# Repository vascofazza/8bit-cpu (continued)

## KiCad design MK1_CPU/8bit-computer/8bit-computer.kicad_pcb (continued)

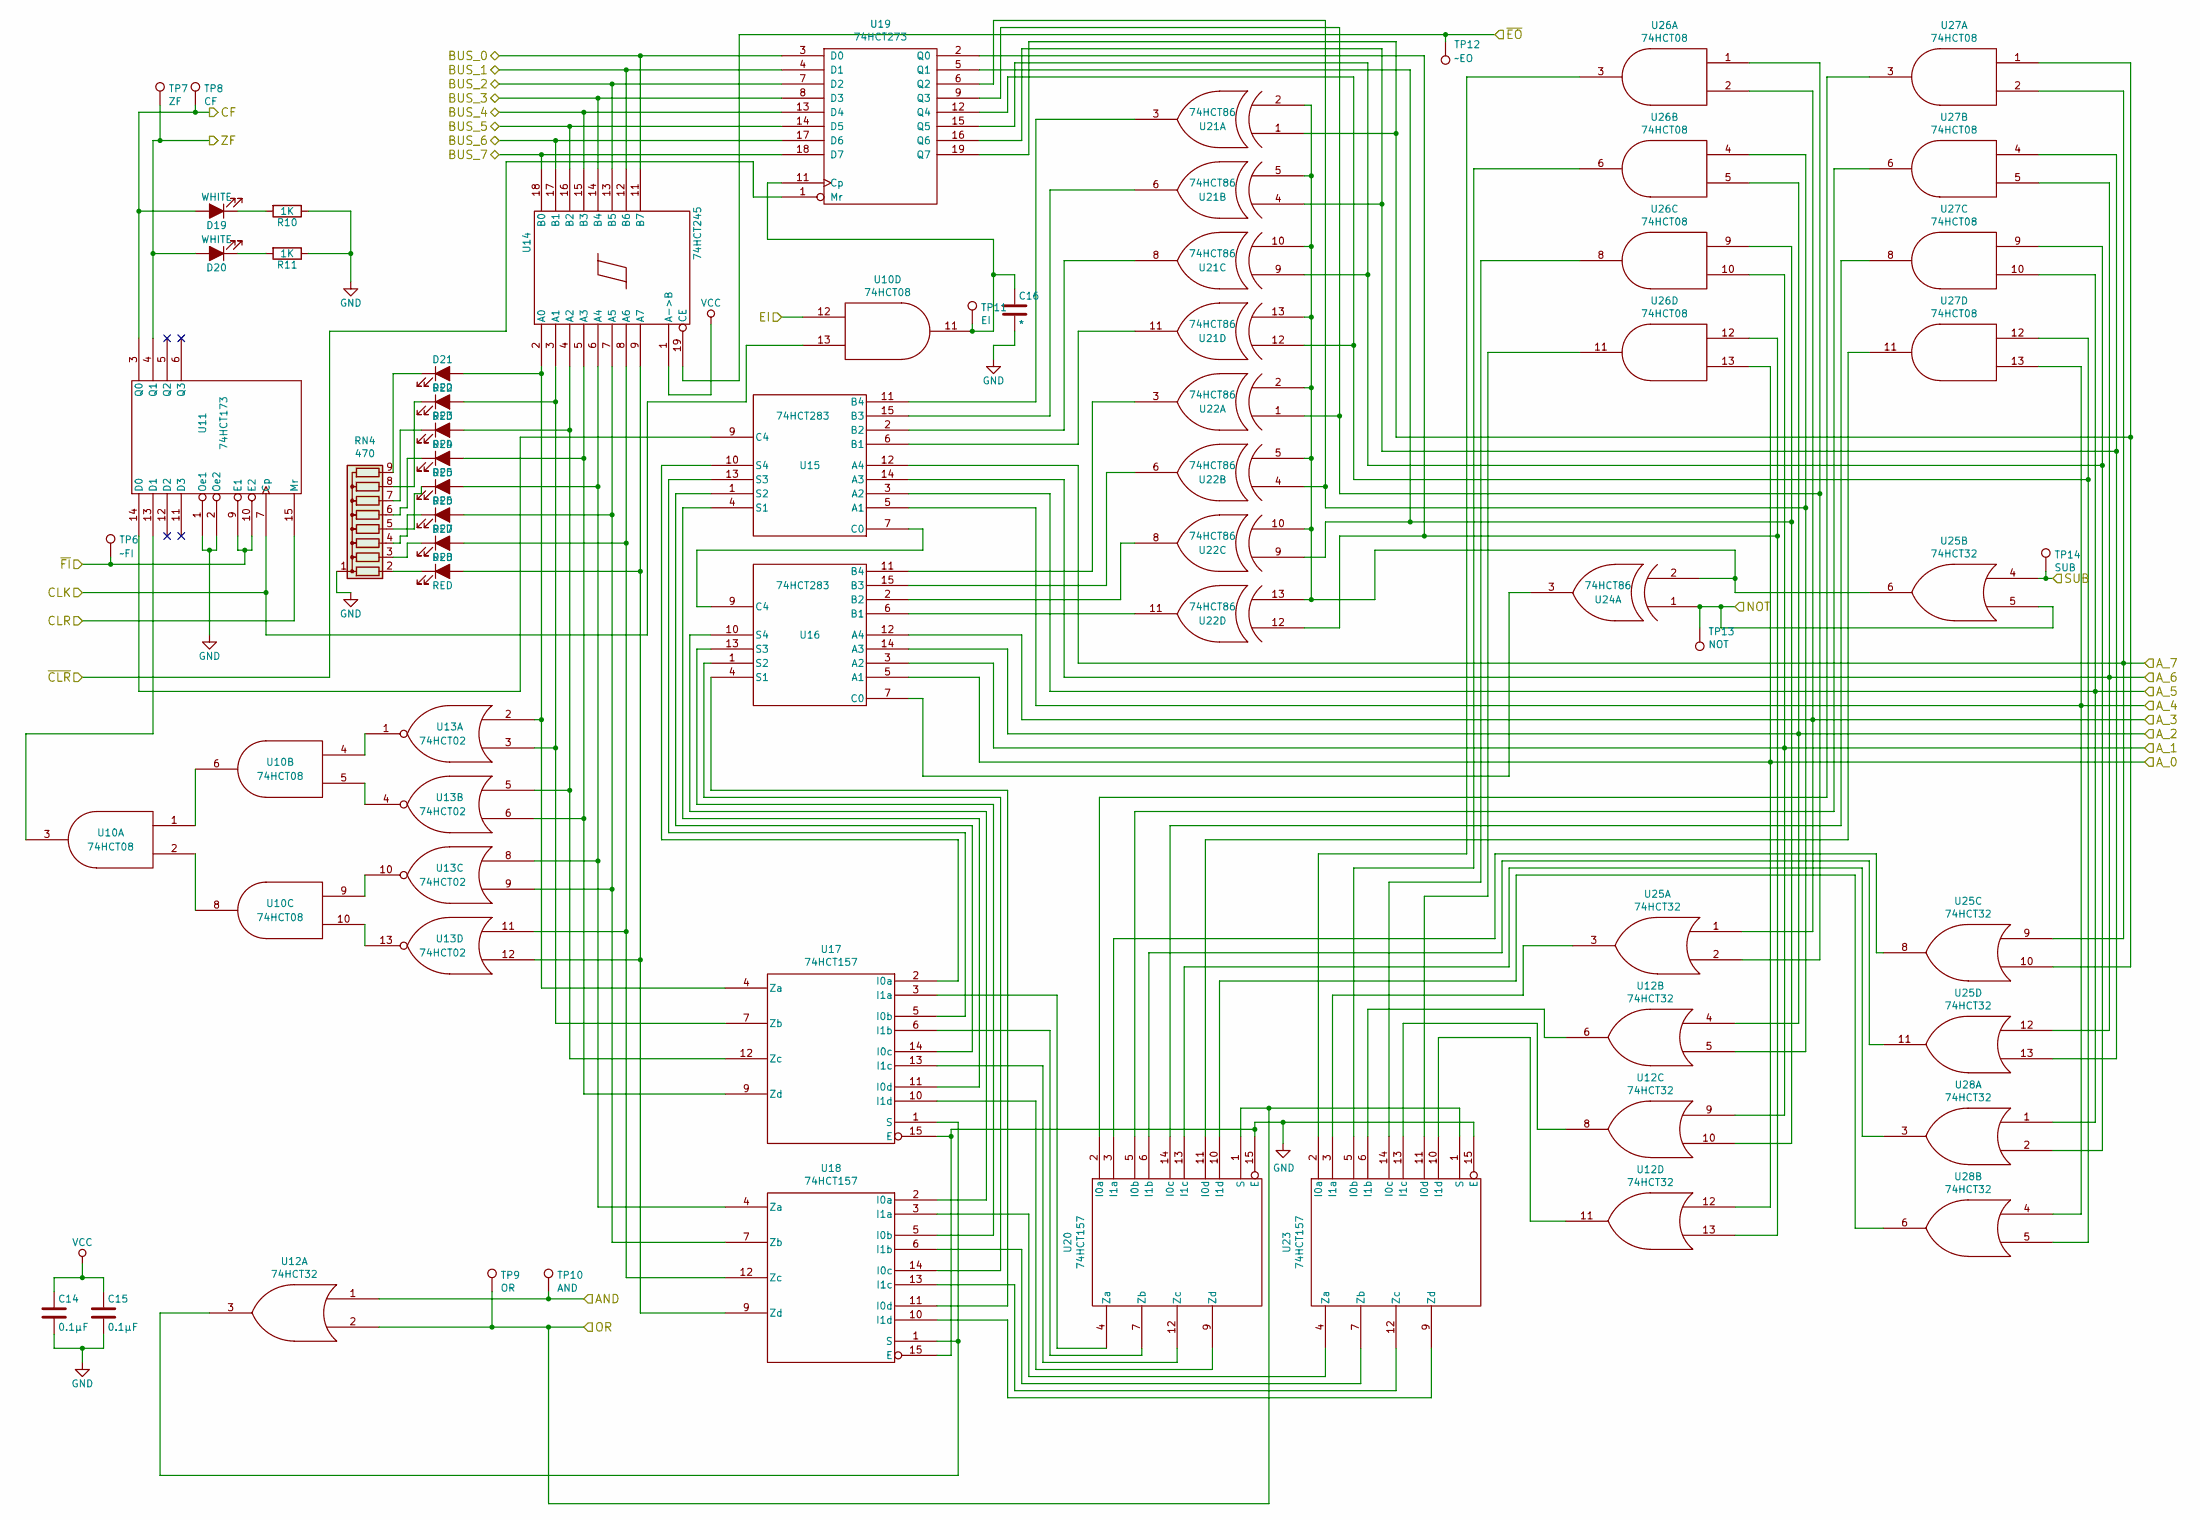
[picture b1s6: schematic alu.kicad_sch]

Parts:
C14, C15: 0.1µF; C_Disc_D4.3mm_W1.9mm_P5.00mm
C16: *; C_Disc_D4.3mm_W1.9mm_P5.00mm
D19, D20: WHITE; LED_D3.0mm
D21, D22, D23, D24, D25, D26, D27, D28: RED; LED_D3.0mm
R10, R11: 1K; R_Axial_DIN0207_L6.3mm_D2.5mm_P7.62mm_Horizontal
RN4: 470; R_Array_SIP9
TP6: ~FI; TestPoint_Pad_1.0x1.0mm
TP7: ZF; TestPoint_Pad_1.0x1.0mm
TP8: CF; TestPoint_Pad_1.0x1.0mm
TP9: OR; TestPoint_Pad_1.0x1.0mm
TP10: AND; TestPoint_Pad_1.0x1.0mm
TP11: EI; TestPoint_Pad_1.0x1.0mm
TP12: ~EO; TestPoint_Pad_1.0x1.0mm
TP13: NOT; TestPoint_Pad_1.0x1.0mm
TP14: SUB; TestPoint_Pad_1.0x1.0mm
U10, U26, U27: 74HCT08; DIP-14_W7.62mm
U11: 74HCT173; DIP-16_W7.62mm
U12, U25, U28: 74HCT32; DIP-14_W7.62mm
U13: 74HCT02; DIP-14_W7.62mm
U14: 74HCT245; DIP-20_W7.62mm
U15, U16: 74HCT283; DIP-16_W7.62mm
U17, U18, U20, U23: 74HCT157; DIP-16_W7.62mm
U19: 74HCT273; DIP-20_W7.62mm
U21, U22, U24: 74HCT86; DIP-14_W7.62mm

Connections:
/ALU/CF: D19.2 (A), TP8.1, U11.3 (Q0); also elsewhere on the board
/ALU/NOT: TP13.1, U24.1 (IN1), U25.5; also elsewhere on the board
/ALU/OR: TP9.1, U12.2, U20.1 (S), U23.1 (S); also elsewhere on the board
/ALU/SUB: TP14.1, U25.4; also elsewhere on the board
/ALU/ZF: D20.2 (A), TP7.1, U11.4 (Q1); also elsewhere on the board
/ALU/~EO: TP12.1, U14.19 (CE); also elsewhere on the board
/ALU/~FI: TP6.1, U11.9 (E1), U11.10 (E2); also elsewhere on the board
/A_0: U12.12, U16.5 (A1), U26.13; also elsewhere on the board
/A_1: U12.9, U16.3 (A2), U26.10; also elsewhere on the board
/A_2: U12.4, U16.14 (A3), U26.5; also elsewhere on the board
/A_3: U16.12 (A4), U25.1, U26.2; also elsewhere on the board
/A_4: U15.5 (A1), U27.13, U28.4; also elsewhere on the board
/A_5: U15.3 (A2), U27.10, U28.1; also elsewhere on the board
/A_6: U15.14 (A3), U25.12, U27.5; also elsewhere on the board
/A_7: U15.12 (A4), U25.9, U27.2; also elsewhere on the board
/BUS_4: U14.15 (B3), U19.13 (D4); also elsewhere on the board
/BUS_5: U14.16 (B2), U19.14 (D5); also elsewhere on the board
/BUS_6: U14.17 (B1), U19.17 (D6); also elsewhere on the board
/BUS_7: U14.18 (B0), U19.18 (D7); also elsewhere on the board
unnamed: C16.1, TP11.1, U10.11, U19.11 (Cp)
unnamed: D19.1 (K), R10.2
unnamed: D20.1 (K), R11.2
unnamed: D21.1 (K), RN4.9 (R8)
unnamed: D21.2 (A), U13.2, U14.2 (A0), U17.4 (Za)
unnamed: D22.1 (K), RN4.8 (R7)
unnamed: D22.2 (A), U13.3, U14.3 (A1), U17.7 (Zb)
unnamed: D23.1 (K), RN4.7 (R6)
unnamed: D23.2 (A), U13.5, U14.4 (A2), U17.12 (Zc)
unnamed: D24.1 (K), RN4.6 (R5)
unnamed: D24.2 (A), U13.6, U14.5 (A3), U17.9 (Zd)
unnamed: D25.1 (K), RN4.5 (R4)
unnamed: D25.2 (A), U13.8, U14.6 (A4), U18.4 (Za)
unnamed: D26.1 (K), RN4.4 (R3)
unnamed: D26.2 (A), U13.9, U14.7 (A5), U18.7 (Zb)
unnamed: D27.1 (K), RN4.3 (R2)
unnamed: D27.2 (A), U13.11, U14.8 (A6), U18.12 (Zc)
unnamed: D28.1 (K), RN4.2 (R1)
unnamed: D28.2 (A), U13.12, U14.9 (A7), U18.9 (Zd)
unnamed: U10.1, U10.6
unnamed: U10.2, U10.8
unnamed: U10.3, U11.13 (D1)
unnamed: U10.4, U13.1
unnamed: U10.5, U13.4
unnamed: U10.9, U13.10
unnamed: U10.10, U13.13
unnamed: U11.14 (D0), U15.9 (C4)
unnamed: U12.3, U17.1 (S), U18.1 (S)
unnamed: U12.5, U19.6 (Q2), U22.4 (IN1), U26.4
unnamed: U12.6, U23.6 (I1b)
unnamed: U12.8, U23.13 (I1c)
unnamed: U12.10, U19.5 (Q1), U22.9 (IN1), U26.9
unnamed: U12.11, U23.10 (I1d)
unnamed: U12.13, U19.2 (Q0), U22.12 (IN1), U26.12
unnamed: U15.1 (S2), U17.14 (I0c)
unnamed: U15.2 (B2), U21.8 (OUT)
unnamed: U15.4 (S1), U17.11 (I0d)
unnamed: U15.6 (B1), U21.11 (OUT)
unnamed: U15.7 (C0), U16.9 (C4)
unnamed: U15.10 (S4), U17.2 (I0a)
unnamed: U15.11 (B4), U21.3 (OUT)
unnamed: U15.13 (S3), U17.5 (I0b)
unnamed: U15.15 (B3), U21.6 (OUT)
unnamed: U16.1 (S2), U18.14 (I0c)
unnamed: U16.2 (B2), U22.8 (OUT)
unnamed: U16.4 (S1), U18.11 (I0d)
unnamed: U16.6 (B1), U22.11 (OUT)
unnamed: U16.7 (C0), U24.3 (OUT)
unnamed: U16.10 (S4), U18.2 (I0a)
unnamed: U16.11 (B4), U22.3 (OUT)
unnamed: U16.13 (S3), U18.5 (I0b)
unnamed: U16.15 (B3), U22.6 (OUT)
unnamed: U17.3 (I1a), U20.4 (Za)
unnamed: U17.6 (I1b), U20.7 (Zb)
unnamed: U17.10 (I1d), U20.9 (Zd)
unnamed: U17.13 (I1c), U20.12 (Zc)
unnamed: U18.3 (I1a), U23.4 (Za)
unnamed: U18.6 (I1b), U23.7 (Zb)
unnamed: U18.10 (I1d), U23.9 (Zd)
unnamed: U18.13 (I1c), U23.12 (Zc)
unnamed: U19.9 (Q3), U22.1 (IN1), U25.2, U26.1
unnamed: U19.12 (Q4), U21.12 (IN1), U27.12, U28.5
unnamed: U19.15 (Q5), U21.9 (IN1), U27.9, U28.2
unnamed: U19.16 (Q6), U21.4 (IN1), U25.13, U27.4
unnamed: U19.19 (Q7), U21.1 (IN1), U25.10, U27.1
unnamed: U20.2 (I0a), U27.3
unnamed: U20.3 (I1a), U25.8
unnamed: U20.5 (I0b), U27.6
unnamed: U20.6 (I1b), U25.11
unnamed: U20.10 (I1d), U28.6
unnamed: U20.11 (I0d), U27.11
unnamed: U20.13 (I1c), U28.3
unnamed: U20.14 (I0c), U27.8
unnamed: U21.2 (IN2), U21.5 (IN2), U21.10 (IN2), U21.13 (IN2), U22.2 (IN2), U22.5 (IN2), U22.10 (IN2), U22.13 (IN2), U24.2 (IN2), U25.6
unnamed: U23.2 (I0a), U26.3
unnamed: U23.3 (I1a), U25.3
unnamed: U23.5 (I0b), U26.6
unnamed: U23.11 (I0d), U26.11
unnamed: U23.14 (I0c), U26.8

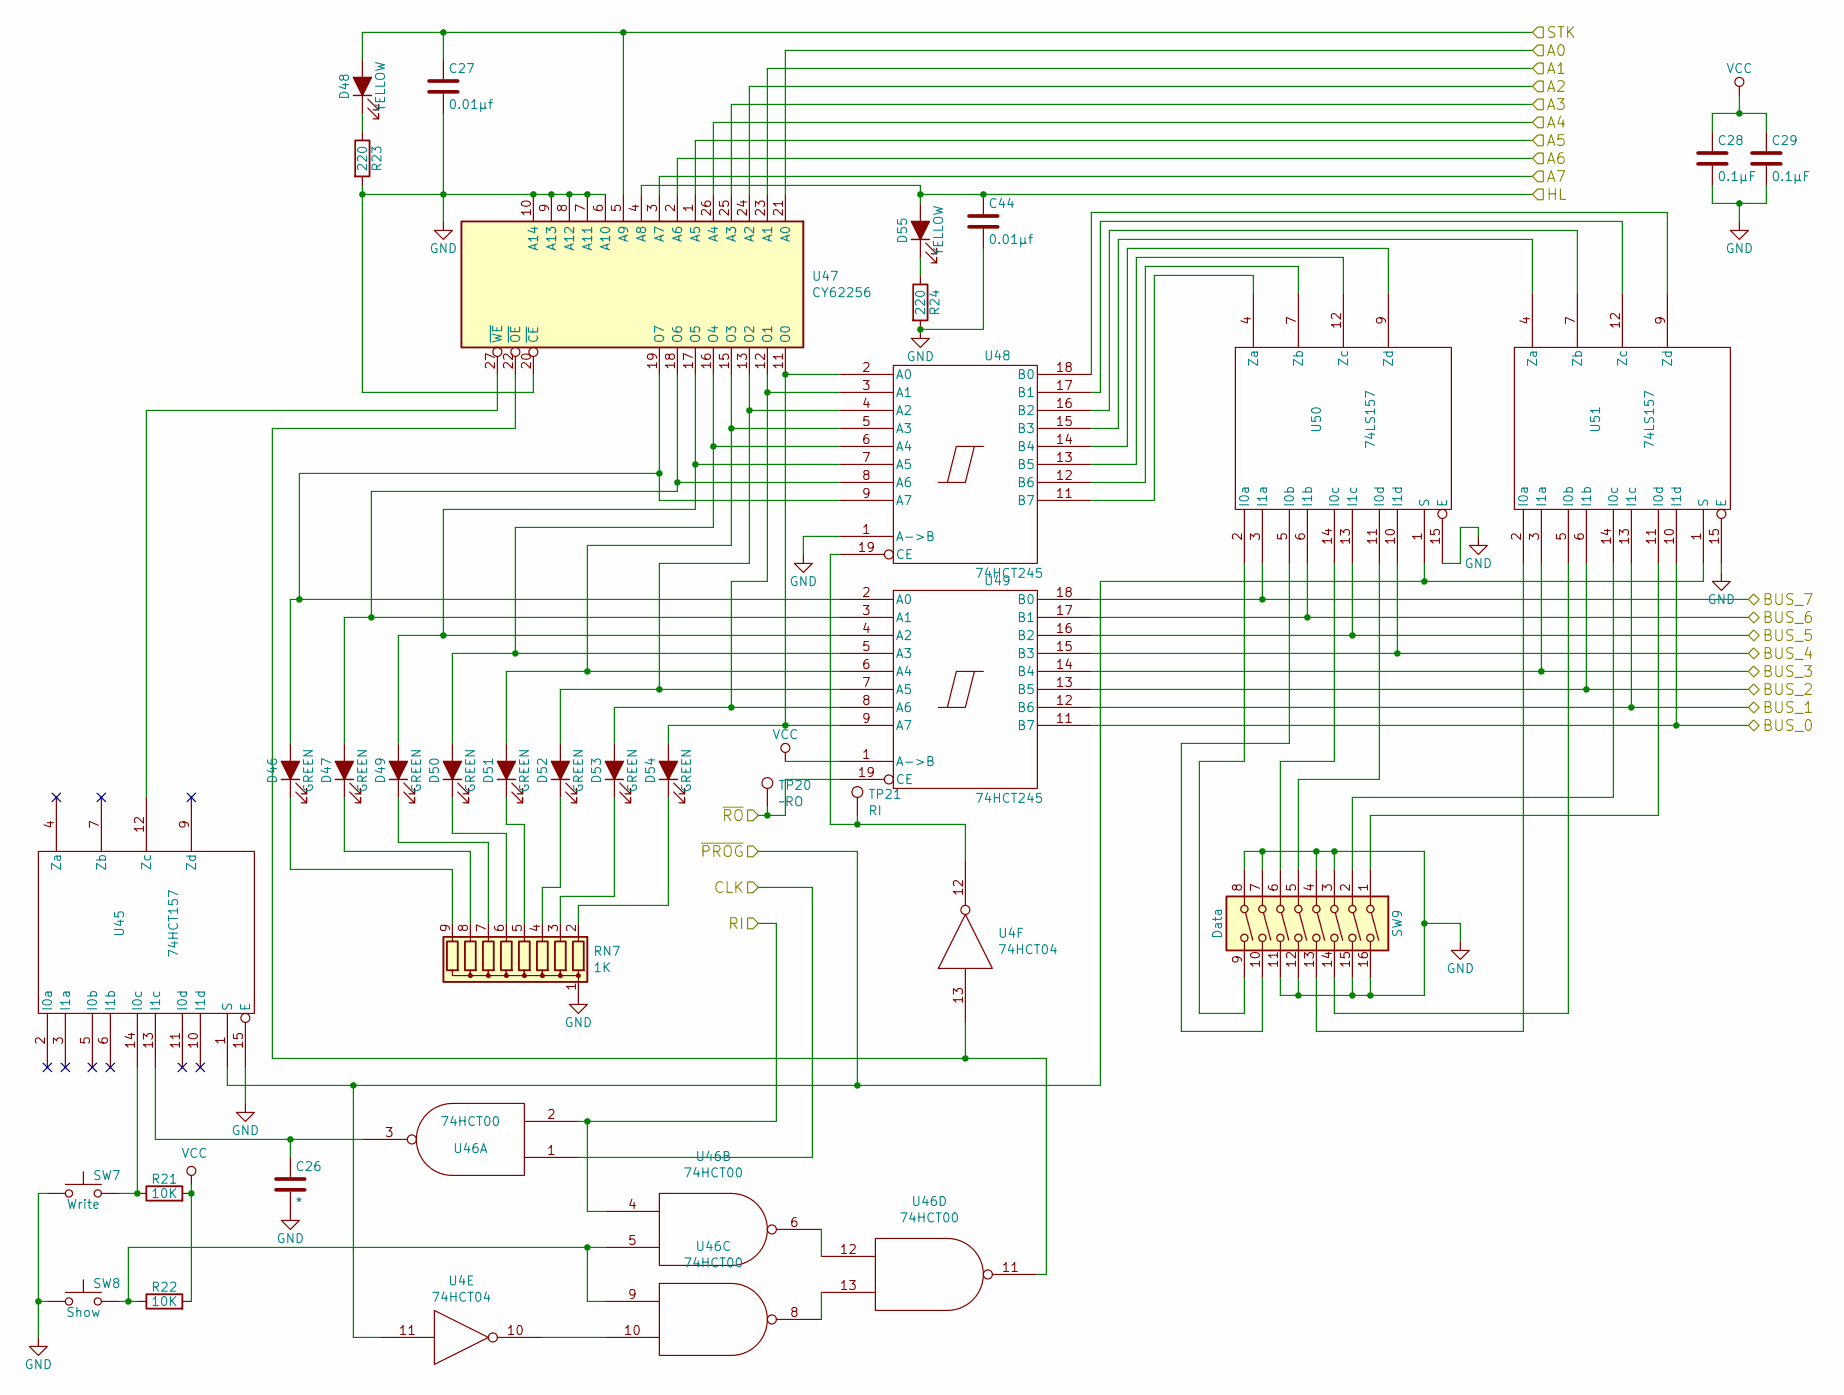
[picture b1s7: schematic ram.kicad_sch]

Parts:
C26: *; C_Disc_D4.3mm_W1.9mm_P5.00mm
C27, C44: 0.01µf; C_Disc_D4.3mm_W1.9mm_P5.00mm
C28, C29: 0.1µF; C_Disc_D4.3mm_W1.9mm_P5.00mm
D46, D47, D49, D50, D51, D52, D53, D54: GREEN; LED_D3.0mm
D48, D55: YELLOW; LED_D3.0mm
R21, R22: 10K; R_Axial_DIN0207_L6.3mm_D2.5mm_P7.62mm_Horizontal
R23, R24: 220; R_Axial_DIN0207_L6.3mm_D2.5mm_P7.62mm_Horizontal
RN7: 1K; R_Array_SIP9
SW7: Write; SW_PUSH_6mm_H5mm
SW8: Show; SW_PUSH_6mm_H5mm
SW9: Data; SW_DIP_SPSTx08_Slide_9.78x22.5mm_W7.62mm_P2.54mm
TP20: ~RO; TestPoint_Pad_1.0x1.0mm
TP21: RI; TestPoint_Pad_1.0x1.0mm
U4: 74HCT04; DIP-14_W7.62mm
U45: 74HCT157; DIP-16_W7.62mm
U46: 74HCT00; DIP-14_W7.62mm
U47: CY62256; DIP-28_W15.24mm_Socket
U48, U49: 74HCT245; DIP-20_W7.62mm
U50, U51: 74LS157; DIP-16_W7.62mm

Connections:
/BUS_4: U49.15 (B3), U50.10 (I1d); also elsewhere on the board
/BUS_5: U49.16 (B2), U50.13 (I1c); also elsewhere on the board
/BUS_6: U49.17 (B1), U50.6 (I1b); also elsewhere on the board
/BUS_7: U49.18 (B0), U50.3 (I1a); also elsewhere on the board
/Control logic/~RO: TP20.1, U49.19 (CE); also elsewhere on the board
/MAR/A0: U47.21 (A0); also elsewhere on the board
/MAR/A1: U47.23 (A1); also elsewhere on the board
/MAR/A2: U47.24 (A2); also elsewhere on the board
/MAR/A3: U47.25 (A3); also elsewhere on the board
/MAR/A4: U47.26 (A4); also elsewhere on the board
/MAR/A5: U47.1 (A5); also elsewhere on the board
/MAR/A6: U47.2 (A6); also elsewhere on the board
/MAR/A7: U47.3 (A7); also elsewhere on the board
/MAR/~PROG: U4.11, U45.1 (S), U50.1 (S), U51.1 (S); also elsewhere on the board
/RAM/HL: C44.1, D55.2 (A), U47.4 (A8); also elsewhere on the board
/RAM/RI: U46.2, U46.4; also elsewhere on the board
/RAM/STK: C27.1, D48.2 (A), U47.5 (A9); also elsewhere on the board
unnamed: C26.1, U45.13 (I1c), U46.3
unnamed: D46.1 (K), RN7.9 (R8)
unnamed: D46.2 (A), U47.19 (O7), U48.9 (A7), U49.2 (A0)
unnamed: D47.1 (K), RN7.8 (R7)
unnamed: D47.2 (A), U47.18 (O6), U48.8 (A6), U49.3 (A1)
unnamed: D48.1 (K), R23.1
unnamed: D49.1 (K), RN7.7 (R6)
unnamed: D49.2 (A), U47.17 (O5), U48.7 (A5), U49.4 (A2)
unnamed: D50.1 (K), RN7.6 (R5)
unnamed: D50.2 (A), U47.16 (O4), U48.6 (A4), U49.5 (A3)
unnamed: D51.1 (K), RN7.5 (R4)
unnamed: D51.2 (A), U47.15 (O3), U48.5 (A3), U49.6 (A4)
unnamed: D52.1 (K), RN7.4 (R3)
unnamed: D52.2 (A), U47.13 (O2), U48.4 (A2), U49.7 (A5)
unnamed: D53.1 (K), RN7.3 (R2)
unnamed: D53.2 (A), U47.12 (O1), U48.3 (A1), U49.8 (A6)
unnamed: D54.1 (K), RN7.2 (R1)
unnamed: D54.2 (A), U47.11 (O0), U48.2 (A0), U49.9 (A7)
unnamed: D55.1 (K), R24.1
unnamed: R21.1, SW7.2, U45.14 (I0c)
unnamed: R22.1, SW8.2, U46.5, U46.9
unnamed: SW9.1, U51.11 (I0d)
unnamed: SW9.2, U51.14 (I0c)
unnamed: SW9.5, U50.11 (I0d)
unnamed: SW9.6, U50.14 (I0c)
unnamed: SW9.9, U50.2 (I0a)
unnamed: SW9.10, U50.5 (I0b)
unnamed: SW9.13, U51.2 (I0a)
unnamed: SW9.14, U51.5 (I0b)
unnamed: TP21.1, U4.12, U48.19 (CE)
unnamed: U4.10, U46.10
unnamed: U4.13, U46.11, U47.22 (~OE)
unnamed: U45.12 (Zc), U47.27 (~WE)
unnamed: U46.6, U46.12
unnamed: U46.8, U46.13
unnamed: U48.11 (B7), U50.4 (Za)
unnamed: U48.12 (B6), U50.7 (Zb)
unnamed: U48.13 (B5), U50.12 (Zc)
unnamed: U48.14 (B4), U50.9 (Zd)
unnamed: U48.15 (B3), U51.4 (Za)
unnamed: U48.16 (B2), U51.7 (Zb)
unnamed: U48.17 (B1), U51.12 (Zc)
unnamed: U48.18 (B0), U51.9 (Zd)

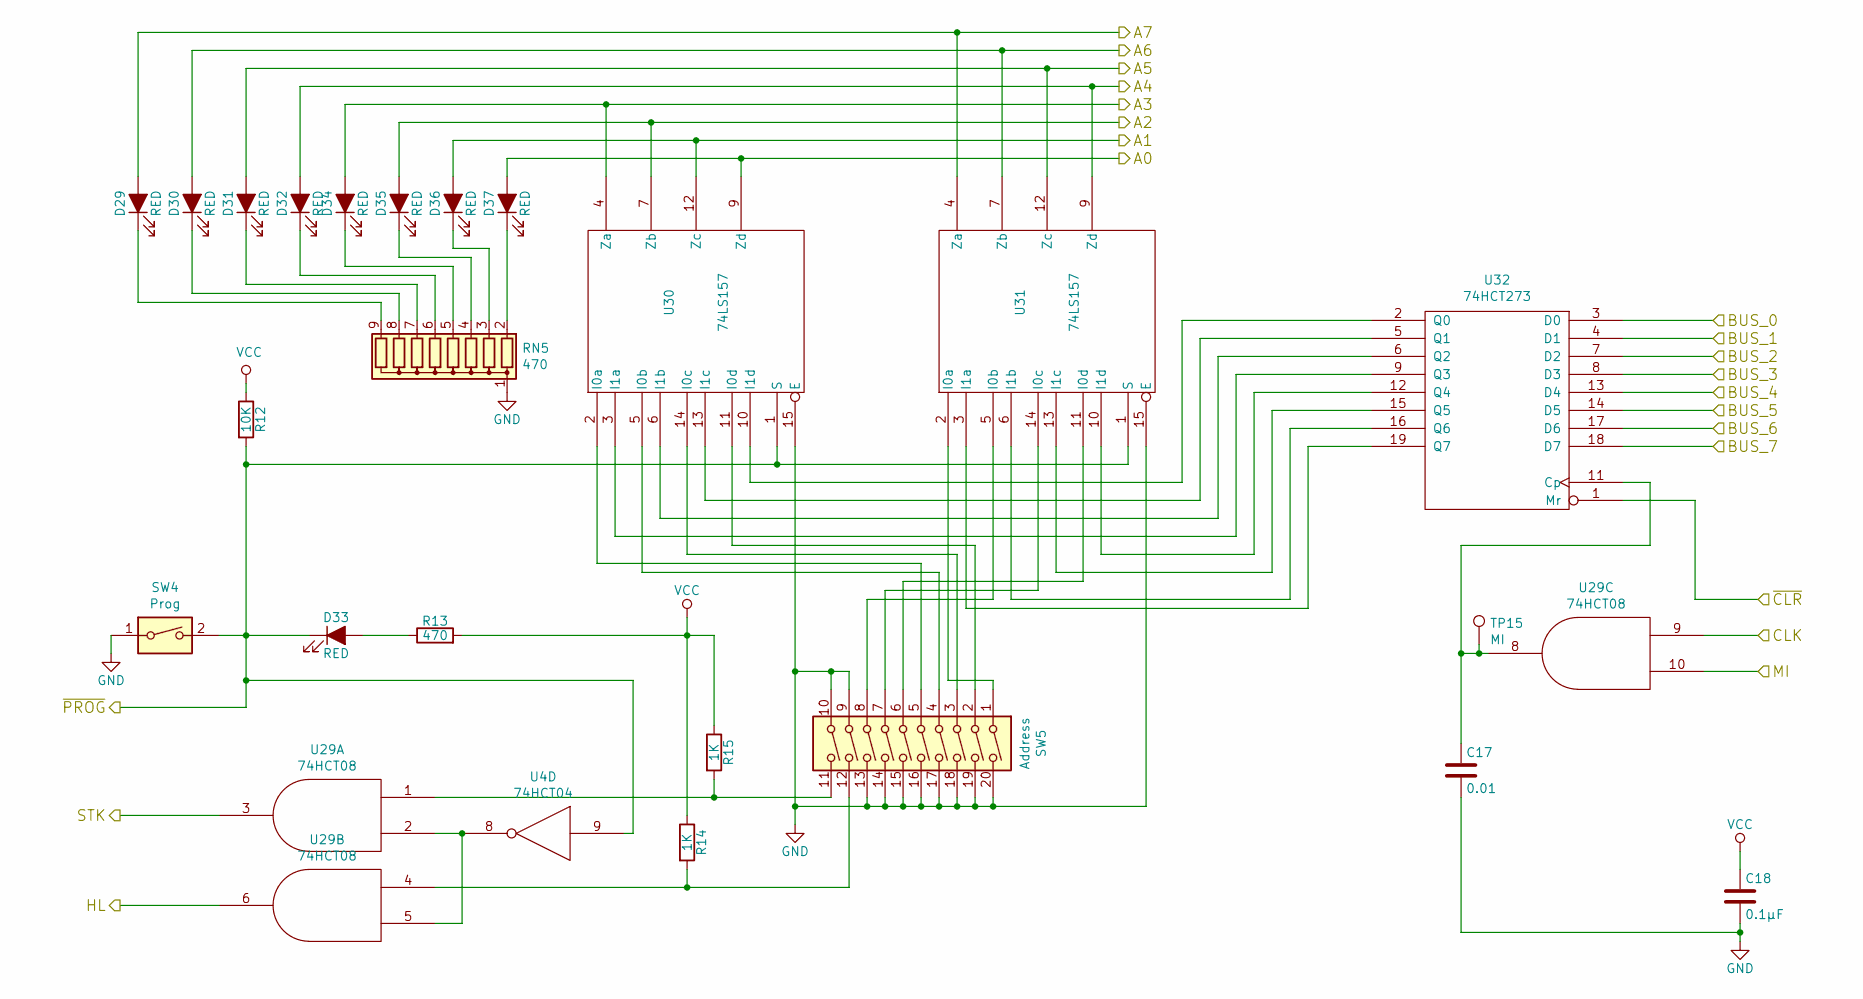
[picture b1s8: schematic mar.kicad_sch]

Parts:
C17: 0.01; C_Disc_D4.3mm_W1.9mm_P5.00mm
C18: 0.1µF; C_Disc_D4.3mm_W1.9mm_P5.00mm
D29, D30, D31, D32, D33, D34, D35, D36, D37: RED; LED_D3.0mm
R12: 10K; R_Axial_DIN0207_L6.3mm_D2.5mm_P7.62mm_Horizontal
R13: 470; R_Axial_DIN0207_L6.3mm_D2.5mm_P7.62mm_Horizontal
R14, R15: 1K; R_Axial_DIN0207_L6.3mm_D2.5mm_P7.62mm_Horizontal
RN5: 470; R_Array_SIP9
SW4: Prog; SW_DIP_SPSTx01_Slide_9.78x4.72mm_W7.62mm_P2.54mm
SW5: Address; SW_DIP_SPSTx10_Slide_9.78x27.58mm_W7.62mm_P2.54mm
TP15: MI; TestPoint_Pad_1.0x1.0mm
U4: 74HCT04; DIP-14_W7.62mm
U29: 74HCT08; DIP-14_W7.62mm
U30, U31: 74LS157; DIP-16_W7.62mm
U32: 74HCT273; DIP-20_W7.62mm

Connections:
/BUS_4: U32.13 (D4); also elsewhere on the board
/BUS_5: U32.14 (D5); also elsewhere on the board
/BUS_6: U32.17 (D6); also elsewhere on the board
/BUS_7: U32.18 (D7); also elsewhere on the board
/MAR/A0: D37.2 (A), U30.9 (Zd); also elsewhere on the board
/MAR/A1: D36.2 (A), U30.12 (Zc); also elsewhere on the board
/MAR/A2: D35.2 (A), U30.7 (Zb); also elsewhere on the board
/MAR/A3: D34.2 (A), U30.4 (Za); also elsewhere on the board
/MAR/A4: D32.2 (A), U31.9 (Zd); also elsewhere on the board
/MAR/A5: D31.2 (A), U31.12 (Zc); also elsewhere on the board
/MAR/A6: D30.2 (A), U31.7 (Zb); also elsewhere on the board
/MAR/A7: D29.2 (A), U31.4 (Za); also elsewhere on the board
/MAR/HL: U29.6; also elsewhere on the board
/MAR/MI: U29.10; also elsewhere on the board
/MAR/STK: U29.3; also elsewhere on the board
/MAR/~PROG: D33.1 (K), R12.2, SW4.2, U4.9, U30.1 (S), U31.1 (S); also elsewhere on the board
unnamed: C17.1, TP15.1, U29.8, U32.11 (Cp)
unnamed: D29.1 (K), RN5.9 (R8)
unnamed: D30.1 (K), RN5.8 (R7)
unnamed: D31.1 (K), RN5.7 (R6)
unnamed: D32.1 (K), RN5.6 (R5)
unnamed: D33.2 (A), R13.1
unnamed: D34.1 (K), RN5.5 (R4)
unnamed: D35.1 (K), RN5.4 (R3)
unnamed: D36.1 (K), RN5.3 (R2)
unnamed: D37.1 (K), RN5.2 (R1)
unnamed: R14.2, SW5.12, U29.4
unnamed: R15.2, SW5.11, U29.1
unnamed: SW5.1, U31.2 (I0a)
unnamed: SW5.2, U30.11 (I0d)
unnamed: SW5.3, U30.14 (I0c)
unnamed: SW5.4, U30.5 (I0b)
unnamed: SW5.5, U30.2 (I0a)
unnamed: SW5.6, U31.11 (I0d)
unnamed: SW5.7, U31.14 (I0c)
unnamed: SW5.8, U31.5 (I0b)
unnamed: U4.8, U29.2, U29.5
unnamed: U30.3 (I1a), U32.9 (Q3)
unnamed: U30.6 (I1b), U32.6 (Q2)
unnamed: U30.10 (I1d), U32.2 (Q0)
unnamed: U30.13 (I1c), U32.5 (Q1)
unnamed: U31.3 (I1a), U32.19 (Q7)
unnamed: U31.6 (I1b), U32.16 (Q6)
unnamed: U31.10 (I1d), U32.12 (Q4)
unnamed: U31.13 (I1c), U32.15 (Q5)

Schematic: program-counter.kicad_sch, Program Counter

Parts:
C24: 0.01µf; C_Disc_D4.3mm_W1.9mm_P5.00mm
C25: 0.1µF; C_Disc_D4.3mm_W1.9mm_P5.00mm
D38, D39, D40, D41, D42, D43, D44, D45: YELLOW; LED_D3.0mm
RN6: 220; R_Array_SIP9
TP17: ~PO; TestPoint_Pad_1.0x1.0mm
TP18: PE; TestPoint_Pad_1.0x1.0mm
TP19: ~PI; TestPoint_Pad_1.0x1.0mm
U42: 74HCT245; DIP-20_W7.62mm
U43, U44: 74HCT161; DIP-16_W7.62mm

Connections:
/BUS_4: U42.9 (A7), U44.3 (P0); also elsewhere on the board
/BUS_5: U42.8 (A6), U44.4 (P1); also elsewhere on the board
/BUS_6: U42.7 (A5), U44.5 (P2); also elsewhere on the board
/BUS_7: U42.6 (A4), U44.6 (P3); also elsewhere on the board
/Control logic/~PO: TP17.1, U42.19 (CE); also elsewhere on the board
unnamed: D38.1 (K), RN6.2 (R1)
unnamed: D38.2 (A), U42.14 (B4), U44.11 (Q3)
unnamed: D39.1 (K), RN6.3 (R2)
unnamed: D39.2 (A), U42.13 (B5), U44.12 (Q2)
unnamed: D40.1 (K), RN6.4 (R3)
unnamed: D40.2 (A), U42.12 (B6), U44.13 (Q1)
unnamed: D41.1 (K), RN6.5 (R4)
unnamed: D41.2 (A), U42.11 (B7), U44.14 (Q0)
unnamed: D42.1 (K), RN6.6 (R5)
unnamed: D42.2 (A), U42.18 (B0), U43.11 (Q3)
unnamed: D43.1 (K), RN6.7 (R6)
unnamed: D43.2 (A), U42.17 (B1), U43.12 (Q2)
unnamed: D44.1 (K), RN6.8 (R7)
unnamed: D44.2 (A), U42.16 (B2), U43.13 (Q1)
unnamed: D45.1 (K), RN6.9 (R8)
unnamed: D45.2 (A), U42.15 (B3), U43.14 (Q0)
unnamed: U43.15 (Tc), U44.7 (Cep), U44.10 (Cet)

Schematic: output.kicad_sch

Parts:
C19, C20: 0.01µF; C_Disc_D4.3mm_W1.9mm_P5.00mm
C21: *; C_Disc_D4.3mm_W1.9mm_P5.00mm
C22, C23: 0.1µF; C_Disc_D4.3mm_W1.9mm_P5.00mm
R16: 100K; R_Axial_DIN0207_L6.3mm_D2.5mm_P7.62mm_Horizontal
R17: 1K; R_Axial_DIN0207_L6.3mm_D2.5mm_P7.62mm_Horizontal
R18, R19, R20: 10K; R_Axial_DIN0207_L6.3mm_D2.5mm_P7.62mm_Horizontal
SW6: Mode; SW_DIP_SPSTx03_Slide_9.78x9.8mm_W7.62mm_P2.54mm
TP16: OI; TestPoint_Pad_1.0x1.0mm
U29: 74HCT08; DIP-14_W7.62mm
U33: NE555; DIP-8_W7.62mm
U34: 74HCT273; DIP-20_W7.62mm
U35: 74HCT107; DIP-14_W7.62mm
U36: 28C64; DIP-28_W15.24mm_Socket
U37, U39, U40, U41: 7SEGMENT_CC; 7SegmentLED_LTS6760_LTS6780
U38: 74HCT139; DIP-16_W7.62mm

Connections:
/BUS_4: U34.13 (D4); also elsewhere on the board
/BUS_5: U34.14 (D5); also elsewhere on the board
/BUS_6: U34.17 (D6); also elsewhere on the board
/BUS_7: U34.18 (D7); also elsewhere on the board
/Control logic/OI: U29.12; also elsewhere on the board
unnamed: C19.1, R16.2, U33.2 (TR), U33.6 (THR)
unnamed: C20.1, U33.5 (CV)
unnamed: C21.1, TP16.1, U29.11, U34.11 (Cp)
unnamed: R16.1, R17.2, U33.7 (DIS)
unnamed: R18.1, SW6.4, U36.2 (A12)
unnamed: R19.1, SW6.5, U36.23 (A11)
unnamed: R20.1, SW6.6, U36.21 (A10)
unnamed: U33.3 (Q), U35.12 (C)
unnamed: U34.2 (Q0), U36.10 (A0)
unnamed: U34.5 (Q1), U36.9 (A1)
unnamed: U34.6 (Q2), U36.8 (A2)
unnamed: U34.9 (Q3), U36.7 (A3)
unnamed: U34.12 (Q4), U36.6 (A4)
unnamed: U34.15 (Q5), U36.5 (A5)
unnamed: U34.16 (Q6), U36.4 (A6)
unnamed: U34.19 (Q7), U36.3 (A7)
unnamed: U35.2 (~Q), U35.9 (C), U36.25 (A8), U38.2 (A0)
unnamed: U35.6 (~Q), U36.24 (A9), U38.3 (A1)
unnamed: U36.11 (D0), U37.10 (G), U39.10 (G), U40.10 (G), U41.10 (G)
unnamed: U36.12 (D1), U37.9 (F), U39.9 (F), U40.9 (F), U41.9 (F)
unnamed: U36.13 (D2), U37.1 (E), U39.1 (E), U40.1 (E), U41.1 (E)
unnamed: U36.15 (D3), U37.2 (D), U39.2 (D), U40.2 (D), U41.2 (D)
unnamed: U36.16 (D4), U37.4 (C), U39.4 (C), U40.4 (C), U41.4 (C)
unnamed: U36.17 (D5), U37.6 (B), U39.6 (B), U40.6 (B), U41.6 (B)
unnamed: U36.18 (D6), U37.7 (A), U39.7 (A), U40.7 (A), U41.7 (A)
unnamed: U36.19 (D7), U37.5 (DP), U39.5 (DP), U40.5 (DP), U41.5 (DP)
unnamed: U37.3 (CC), U37.8 (CC), U38.7 (O3)
unnamed: U38.4 (O0), U41.3 (CC), U41.8 (CC)
unnamed: U38.5 (O1), U40.3 (CC), U40.8 (CC)
unnamed: U38.6 (O2), U39.3 (CC), U39.8 (CC)

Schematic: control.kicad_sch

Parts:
C39: 0.01µF; C_Disc_D4.3mm_W1.9mm_P5.00mm
C40, C41: 0.1µF; C_Disc_D4.3mm_W1.9mm_P5.00mm
D90, D91, D92: YELLOW; LED_D3.0mm
D93, D94, D95, D96, D97, D98, D99, D100, D101, D102, D103, D104, D105, D106, D107, D108, D109, D110, D111, D112, D113, D114, D115, D116, D117, D118, D119, D120, D121, D122, D123, D124, D125, D126: BLUE; LED_D3.0mm
R29, R30, R31, R32: 10K; R_Axial_DIN0207_L6.3mm_D2.5mm_P7.62mm_Horizontal
RN13, RN14, RN15, RN16, RN17, RN18, RN19: 1K; R_Array_SIP9
SW10: Reset; SW_PUSH_6mm_H5mm
TP39: ~CU_EN; TestPoint_Pad_1.0x1.0mm
U24: 74HCT86; DIP-14_W7.62mm
U60: 74HCT04; DIP-14_W7.62mm
U72: 74HCT161; DIP-16_W7.62mm
U73, U74, U75, U76: AM29F040; PLCC-32_THT-Socket
U77: 74HCT138; DIP-16_W7.62mm
U78, U79: 74HCT238; DIP-16_W7.62mm

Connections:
/A register/RGT: U76.18 (D4); also elsewhere on the board
/A register/ROT: D94.2 (A), U79.10 (Y5); also elsewhere on the board
/A register/~AO: D106.1 (K), U77.14 (O1); also elsewhere on the board
/ALU/CF: U73.25 (A11), U74.25 (A11), U75.25 (A11), U76.25 (A11); also elsewhere on the board
/ALU/NOT: D125.2 (A), U79.7 (Y7); also elsewhere on the board
/ALU/OR: D124.2 (A), U79.13 (Y2); also elsewhere on the board
/ALU/SUB: D122.2 (A), U79.14 (Y1); also elsewhere on the board
/ALU/ZF: U73.4 (A12), U74.4 (A12), U75.4 (A12), U76.4 (A12); also elsewhere on the board
/ALU/~EO: D116.1 (K), U77.7 (O7); also elsewhere on the board
/ALU/~FI: U60.8; also elsewhere on the board
/Control logic/E0: D103.2 (A), RN16.4 (R3), U76.21 (D7); also elsewhere on the board
/Control logic/E1: D105.2 (A), RN16.3 (R2), U76.20 (D6); also elsewhere on the board
/Control logic/EXT_I: RN15.2 (R1), U74.19 (D5); also elsewhere on the board
/Control logic/HL: RN16.2 (R1), U76.19 (D5); also elsewhere on the board
/Control logic/II: D100.2 (A), U74.21 (D7); also elsewhere on the board
/Control logic/IRQ0: U73.28 (A13), U74.28 (A13), U75.28 (A13), U76.28 (A13); also elsewhere on the board
/Control logic/IRQ1: U73.29 (A14), U74.29 (A14), U75.29 (A14), U76.29 (A14); also elsewhere on the board
/Control logic/MI: D95.2 (A), RN15.3 (R2), U73.14 (D1); also elsewhere on the board
/Control logic/OI: D101.2 (A), R32.1, U74.20 (D6); also elsewhere on the board
/Control logic/RI: D96.2 (A), RN15.4 (R3), U73.13 (D0); also elsewhere on the board
/Control logic/SD: D99.2 (A), R30.1, U75.15 (D2); also elsewhere on the board
/Control logic/STK: RN15.6 (R5), U73.20 (D6); also elsewhere on the board
/Control logic/U0: D107.2 (A), U75.14 (D1); also elsewhere on the board
/Control logic/U1: D109.2 (A), U75.13 (D0); also elsewhere on the board
/Control logic/~BO: D110.1 (K), U77.13 (O2); also elsewhere on the board
/Control logic/~CO: D112.1 (K), U77.12 (O3); also elsewhere on the board
/Control logic/~DO: D114.1 (K), U77.11 (O4); also elsewhere on the board
/Control logic/~PO: D120.1 (K), U77.10 (O5); also elsewhere on the board
/Control logic/~RO: U60.10; also elsewhere on the board
/Control logic/~SO: D118.1 (K), U77.9 (O6); also elsewhere on the board
/IR_0: U73.9 (A3), U74.9 (A3), U75.9 (A3), U76.9 (A3); also elsewhere on the board
/IR_1: U73.8 (A4), U74.8 (A4), U75.8 (A4), U76.8 (A4); also elsewhere on the board
/IR_2: U73.7 (A5), U74.7 (A5), U75.7 (A5), U76.7 (A5); also elsewhere on the board
/IR_3: U73.6 (A6), U74.6 (A6), U75.6 (A6), U76.6 (A6); also elsewhere on the board
/IR_4: U73.5 (A7), U74.5 (A7), U75.5 (A7), U76.5 (A7); also elsewhere on the board
/IR_5: U73.27 (A8), U74.27 (A8), U75.27 (A8), U76.27 (A8); also elsewhere on the board
/IR_6: U73.26 (A9), U74.26 (A9), U75.26 (A9), U76.26 (A9); also elsewhere on the board
/IR_7: U73.23 (A10), U74.23 (A10), U75.23 (A10), U76.23 (A10); also elsewhere on the board
/PC Interface/CLR: R29.1, SW10.1, U60.3; also elsewhere on the board
/PC Interface/CU_DIS: RN13.5 (R4), TP39.1, U73.24 (~OE), U74.24 (~OE), U75.24 (~OE), U76.24 (~OE); also elsewhere on the board
/~CLK: U72.2 (Cp); also elsewhere on the board
unnamed: C39.1, RN13.9 (R8), U24.4 (IN1), U76.13 (D0)
unnamed: D90.1 (K), RN13.2 (R1)
unnamed: D90.2 (A), U72.14 (Q0), U73.12 (A0), U74.12 (A0), U75.12 (A0), U76.12 (A0)
unnamed: D91.1 (K), RN13.3 (R2)
unnamed: D91.2 (A), U72.13 (Q1), U73.11 (A1), U74.11 (A1), U75.11 (A1), U76.11 (A1)
unnamed: D92.1 (K), RN13.4 (R3)
unnamed: D92.2 (A), U72.12 (Q2), U73.10 (A2), U74.10 (A2), U75.10 (A2), U76.10 (A2)
unnamed: D93.1 (K), RN14.9 (R8)
unnamed: D94.1 (K), RN13.6 (R5)
unnamed: D95.1 (K), RN14.8 (R7)
unnamed: D96.1 (K), RN14.7 (R6)
unnamed: D97.1 (K), RN13.7 (R6)
unnamed: D98.1 (K), RN14.6 (R5)
unnamed: D98.2 (A), RN16.6 (R5), U60.11, U74.14 (D1)
unnamed: D99.1 (K), RN19.9 (R8)
unnamed: D100.1 (K), RN14.5 (R4)
unnamed: D101.1 (K), RN19.8 (R7)
unnamed: D102.1 (K), RN14.4 (R3)
unnamed: D102.2 (A), U60.9, U75.18 (D4)
unnamed: D103.1 (K), RN19.7 (R6)
unnamed: D104.1 (K), RN14.3 (R2)
unnamed: D105.1 (K), RN19.6 (R5)
unnamed: D106.2 (A), RN17.9 (R8)
unnamed: D107.1 (K), RN19.5 (R4)
unnamed: D108.1 (K), RN14.2 (R1)
unnamed: D109.1 (K), RN19.4 (R3)
unnamed: D110.2 (A), RN17.8 (R7)
unnamed: D111.1 (K), RN18.6 (R5)
unnamed: D112.2 (A), RN17.7 (R6)
unnamed: D113.1 (K), RN18.5 (R4)
unnamed: D114.2 (A), RN17.6 (R5)
unnamed: D115.1 (K), RN18.4 (R3)
unnamed: D116.2 (A), RN17.5 (R4)
unnamed: D117.1 (K), RN18.3 (R2)
unnamed: D118.2 (A), RN17.4 (R3)
unnamed: D119.1 (K), RN13.8 (R7)
unnamed: D120.2 (A), RN17.3 (R2)
unnamed: D121.1 (K), RN18.9 (R8)
unnamed: D122.1 (K), RN18.8 (R7)
unnamed: D123.1 (K), RN18.7 (R6)
unnamed: D124.1 (K), RN18.2 (R1)
unnamed: D125.1 (K), RN19.3 (R2)
unnamed: D126.1 (K), RN19.2 (R1)
unnamed: RN16.7 (R6), U74.18 (D4), U77.1 (A0)
unnamed: RN16.8 (R7), U74.17 (D3), U77.2 (A1)
unnamed: RN16.9 (R8), U74.15 (D2), U77.3 (A2)
unnamed: U24.6 (OUT), U72.1 (~MR)
unnamed: U75.21 (D7), U79.1 (A0)

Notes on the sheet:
AND
SUB
NOT
SHF
HLT
ROT

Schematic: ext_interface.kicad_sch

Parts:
C45: 0.01µF; C_Disc_D4.3mm_W1.9mm_P5.00mm
D88, D89: WHITE; LED_D3.0mm
J4: EXT-CONN; PinHeader_2x09_P2.54mm_Vertical
R25, R26, R27, R28: 1K; R_Axial_DIN0207_L6.3mm_D2.5mm_P7.62mm_Horizontal
TP34: E0; TestPoint_Pad_1.0x1.0mm
TP35: EXT_IN; TestPoint_Pad_1.0x1.0mm
TP36: E1; TestPoint_Pad_1.0x1.0mm
TP37: U0; TestPoint_Pad_1.0x1.0mm
TP38: U1; TestPoint_Pad_1.0x1.0mm
U64: 74HCT08; DIP-14_W7.62mm
U69: 74HCT02; DIP-14_W7.62mm
U70: 74HCT245; DIP-20_W7.62mm
U71: 74HCT107; DIP-14_W7.62mm

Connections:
/BUS_4: U70.14 (B4); also elsewhere on the board
/BUS_5: U70.13 (B5); also elsewhere on the board
/BUS_6: U70.12 (B6); also elsewhere on the board
/BUS_7: U70.11 (B7); also elsewhere on the board
/Control logic/E0: J4.5, TP34.1, U64.10, U69.3; also elsewhere on the board
/Control logic/E1: J4.7, TP36.1, U64.5, U69.2; also elsewhere on the board
/Control logic/EXT_I: C45.1, TP35.1, U64.4, U64.9, U70.1 (A->B); also elsewhere on the board
/Control logic/IRQ0: D88.2 (A), U71.3 (Q); also elsewhere on the board
/Control logic/IRQ1: D89.2 (A), U71.5 (Q); also elsewhere on the board
/Control logic/U0: J4.9, TP37.1; also elsewhere on the board
/Control logic/U1: J4.11, TP38.1; also elsewhere on the board
unnamed 137: U64.11; also elsewhere on the board
unnamed: D88.1 (K), R25.2
unnamed: D89.1 (K), R26.2
unnamed: J4.1, R27.1, U71.1 (J)
unnamed: J4.2, U70.2 (A0)
unnamed: J4.3, R28.1, U71.8 (J)
unnamed: J4.4, U70.3 (A1)
unnamed: J4.6, U70.4 (A2)
unnamed: J4.8, U70.5 (A3)
unnamed: J4.10, U70.6 (A4)
unnamed: J4.12, U70.7 (A5)
unnamed: J4.14, U70.8 (A6)
unnamed: J4.16, U70.9 (A7)
unnamed: U64.6, U69.5
unnamed: U64.8, U69.9
unnamed: U69.1, U70.19 (CE)
unnamed: U69.4, U71.10 (~R)
unnamed: U69.10, U71.13 (~R)

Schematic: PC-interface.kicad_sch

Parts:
A1: Arduino Nano; Arduino_Nano
JP1: Arduino_VIN; SolderJumper-2_P1.3mm_Bridged_RoundedPad1.0x1.5mm
RN10: 1K; R_Array_SIP9
U59: 74HCT245; DIP-20_W7.62mm
U60: 74HCT04; DIP-14_W7.62mm

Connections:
/BUS_4: U59.14 (B4); also elsewhere on the board
/BUS_5: U59.13 (B5); also elsewhere on the board
/BUS_6: U59.12 (B6); also elsewhere on the board
/BUS_7: U59.11 (B7); also elsewhere on the board
/Clock/CLK_IN: A1.19 (A0), RN10.5 (R4); also elsewhere on the board
/PC Interface/CLR: A1.20 (A1), RN10.4 (R3); also elsewhere on the board
/PC Interface/CU_DIS: A1.21 (A2), RN10.3 (R2); also elsewhere on the board
/PC Interface/HL: A1.14 (D11), RN10.8 (R7); also elsewhere on the board
/PC Interface/MI: A1.13 (D10), RN10.7 (R6); also elsewhere on the board
/PC Interface/RI: A1.15 (D12), RN10.9 (R8); also elsewhere on the board
unnamed: A1.5 (D2), U59.2 (A0)
unnamed: A1.6 (D3), U59.3 (A1)
unnamed: A1.7 (D4), U59.4 (A2)
unnamed: A1.8 (D5), U59.5 (A3)
unnamed: A1.9 (D6), U59.6 (A4)
unnamed: A1.10 (D7), U59.7 (A5)
unnamed: A1.11 (D8), U59.8 (A6)
unnamed: A1.12 (D9), U59.9 (A7)
unnamed: A1.16 (D13), RN10.6 (R5), U60.1
unnamed: A1.30 (VIN), JP1.1 (A)
unnamed: U59.19 (CE), U60.2

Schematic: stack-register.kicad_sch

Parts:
C30: 0.1µF; C_Disc_D4.3mm_W1.9mm_P5.00mm
C31, C32, C33: *; C_Disc_D4.3mm_W1.9mm_P5.00mm
D56, D57, D58, D59, D60, D61, D62, D63: YELLOW; LED_D3.0mm
RN8: 220; R_Array_SIP9
TP22: ~SO; TestPoint_Pad_1.0x1.0mm
TP23: SU; TestPoint_Pad_1.0x1.0mm
TP24: SD; TestPoint_Pad_1.0x1.0mm
TP25: SI; TestPoint_Pad_1.0x1.0mm
U52: 74HCT245; DIP-20_W7.62mm
U53, U54: 74HCT193; DIP-16_W7.62mm
U55: 74HCT00; DIP-14_W7.62mm

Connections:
/BUS_4: U52.15 (B3), U53.15 (A); also elsewhere on the board
/BUS_5: U52.16 (B2), U53.1 (B); also elsewhere on the board
/BUS_6: U52.17 (B1), U53.10 (C); also elsewhere on the board
/BUS_7: U52.18 (B0), U53.9 (D); also elsewhere on the board
/Control logic/SD: U55.4; also elsewhere on the board
/Control logic/~SO: TP22.1, U52.19 (CE); also elsewhere on the board
unnamed: D56.1 (K), RN8.9 (R8)
unnamed: D57.1 (K), RN8.8 (R7)
unnamed: D58.1 (K), RN8.7 (R6)
unnamed: D59.1 (K), RN8.6 (R5)
unnamed: D60.1 (K), RN8.5 (R4)
unnamed: D61.1 (K), RN8.4 (R3)
unnamed: D62.1 (K), RN8.3 (R2)
unnamed: D63.1 (K), RN8.2 (R1)

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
